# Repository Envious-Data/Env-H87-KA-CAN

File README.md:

# Env-H87-KA-CAN (May be renamed at some point)
Originally meant to be a keyboard for a comission I decided to re-work to a F12 TKL

## Main features
- Native ISO
- Hotswap
- Stepped Capslock (Optional)
- More to come

## Future plans
- Split Space space support
- Some indicator leds
- some kind of cyberpunk-y Lighting
- idk hidden cat symbol somewhere
- Weight but not really a weight

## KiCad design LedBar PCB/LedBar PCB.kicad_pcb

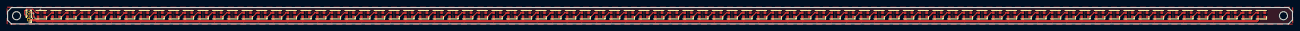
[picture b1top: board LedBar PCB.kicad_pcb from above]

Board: 2 copper layers, 349.7 x 4.4 mm, 88 parts (0 on the bottom side), 86 nets.

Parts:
C1: 100nF 0402; C_0402_1005Metric
D1, D2, D3, D4, D5, D6, D7, D8, D9, D10, D11, D12, D13, D14, D15, D16, D17, D18, D19, D20, D21, D22, D23, D24, D25, D26, D27, D28, D29, D30, D31, D32, D33, D34, D35, D36, D37, D38, D39, D40, D41, D42, D43, D44, D45, D46, D47, D48, D49, D50, D51, D52, D53, D54, D55, D56, D57, D58, D59, D60, D61, D62, D63, D64, D65, D66, D67, D68, D69, D70, D71, D72, D73, D74, D75, D76, D77, D78, D79, D80, D81, D82, D83, D84: WS2812B-2020; LED_WS2812B-2020_PLCC4_2.0x2.0mm
H1, H2: MountingHole; MountingHole_2.2mm_M2
J1: Conn_01x03; PinHeader_1x03_P1.00mm_Vertical

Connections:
+5V: C1.1, D1.4 (VDD), D2.4 (VDD), D3.4 (VDD), D4.4 (VDD), D5.4 (VDD), D6.4 (VDD), D7.4 (VDD), D8.4 (VDD), D9.4 (VDD), D10.4 (VDD), D11.4 (VDD), D12.4 (VDD), D13.4 (VDD), D14.4 (VDD), D15.4 (VDD), D16.4 (VDD), D17.4 (VDD), D18.4 (VDD), D19.4 (VDD), D20.4 (VDD), D21.4 (VDD), D22.4 (VDD), D23.4 (VDD), D24.4 (VDD), D25.4 (VDD), D26.4 (VDD), D27.4 (VDD), D28.4 (VDD), D29.4 (VDD), D30.4 (VDD), D31.4 (VDD), D32.4 (VDD), D33.4 (VDD), D34.4 (VDD), D35.4 (VDD), D36.4 (VDD), D37.4 (VDD), D38.4 (VDD), D39.4 (VDD), D40.4 (VDD), D41.4 (VDD), D42.4 (VDD), D43.4 (VDD), D44.4 (VDD), D45.4 (VDD), D46.4 (VDD), D47.4 (VDD), D48.4 (VDD), D49.4 (VDD), D50.4 (VDD), D51.4 (VDD), D52.4 (VDD), D53.4 (VDD), D54.4 (VDD), D55.4 (VDD), D56.4 (VDD), D57.4 (VDD), D58.4 (VDD), D59.4 (VDD), D60.4 (VDD), D61.4 (VDD), D62.4 (VDD), D63.4 (VDD), D64.4 (VDD), D65.4 (VDD), D66.4 (VDD), D67.4 (VDD), D68.4 (VDD), D69.4 (VDD), D70.4 (VDD), D71.4 (VDD), D72.4 (VDD), D73.4 (VDD), D74.4 (VDD), D75.4 (VDD), D76.4 (VDD), D77.4 (VDD), D78.4 (VDD), D79.4 (VDD), D80.4 (VDD), D81.4 (VDD), D82.4 (VDD), D83.4 (VDD), D84.4 (VDD), J1.1
DataIn: D1.3 (DIN), J1.2
GND: C1.2, D1.2 (VSS), D2.2 (VSS), D3.2 (VSS), D4.2 (VSS), D5.2 (VSS), D6.2 (VSS), D7.2 (VSS), D8.2 (VSS), D9.2 (VSS), D10.2 (VSS), D11.2 (VSS), D12.2 (VSS), D13.2 (VSS), D14.2 (VSS), D15.2 (VSS), D16.2 (VSS), D17.2 (VSS), D18.2 (VSS), D19.2 (VSS), D20.2 (VSS), D21.2 (VSS), D22.2 (VSS), D23.2 (VSS), D24.2 (VSS), D25.2 (VSS), D26.2 (VSS), D27.2 (VSS), D28.2 (VSS), D29.2 (VSS), D30.2 (VSS), D31.2 (VSS), D32.2 (VSS), D33.2 (VSS), D34.2 (VSS), D35.2 (VSS), D36.2 (VSS), D37.2 (VSS), D38.2 (VSS), D39.2 (VSS), D40.2 (VSS), D41.2 (VSS), D42.2 (VSS), D43.2 (VSS), D44.2 (VSS), D45.2 (VSS), D46.2 (VSS), D47.2 (VSS), D48.2 (VSS), D49.2 (VSS), D50.2 (VSS), D51.2 (VSS), D52.2 (VSS), D53.2 (VSS), D54.2 (VSS), D55.2 (VSS), D56.2 (VSS), D57.2 (VSS), D58.2 (VSS), D59.2 (VSS), D60.2 (VSS), D61.2 (VSS), D62.2 (VSS), D63.2 (VSS), D64.2 (VSS), D65.2 (VSS), D66.2 (VSS), D67.2 (VSS), D68.2 (VSS), D69.2 (VSS), D70.2 (VSS), D71.2 (VSS), D72.2 (VSS), D73.2 (VSS), D74.2 (VSS), D75.2 (VSS), D76.2 (VSS), D77.2 (VSS), D78.2 (VSS), D79.2 (VSS), D80.2 (VSS), D81.2 (VSS), D82.2 (VSS), D83.2 (VSS), D84.2 (VSS), J1.3
unnamed: D1.1 (DOUT), D2.3 (DIN)
unnamed: D2.1 (DOUT), D3.3 (DIN)
unnamed: D3.1 (DOUT), D4.3 (DIN)
unnamed: D4.1 (DOUT), D5.3 (DIN)
unnamed: D5.1 (DOUT), D6.3 (DIN)
unnamed: D6.1 (DOUT), D7.3 (DIN)
unnamed: D7.1 (DOUT), D8.3 (DIN)
unnamed: D8.1 (DOUT), D9.3 (DIN)
unnamed: D10.1 (DOUT), D11.3 (DIN)
unnamed: D9.1 (DOUT), D10.3 (DIN)
unnamed: D11.1 (DOUT), D12.3 (DIN)
unnamed: D12.1 (DOUT), D13.3 (DIN)
unnamed: D13.1 (DOUT), D14.3 (DIN)
unnamed: D14.1 (DOUT), D15.3 (DIN)
unnamed: D15.1 (DOUT), D16.3 (DIN)
unnamed: D16.1 (DOUT), D17.3 (DIN)
unnamed: D17.1 (DOUT), D18.3 (DIN)
unnamed: D18.1 (DOUT), D19.3 (DIN)
unnamed: D19.1 (DOUT), D20.3 (DIN)
unnamed: D20.1 (DOUT), D21.3 (DIN)
unnamed: D21.1 (DOUT), D22.3 (DIN)
unnamed: D22.1 (DOUT), D23.3 (DIN)
unnamed: D23.1 (DOUT), D24.3 (DIN)
unnamed: D24.1 (DOUT), D25.3 (DIN)
unnamed: D25.1 (DOUT), D26.3 (DIN)
unnamed: D26.1 (DOUT), D27.3 (DIN)
unnamed: D27.1 (DOUT), D28.3 (DIN)
unnamed: D28.1 (DOUT), D29.3 (DIN)
unnamed: D29.1 (DOUT), D30.3 (DIN)
unnamed: D30.1 (DOUT), D31.3 (DIN)
unnamed: D31.1 (DOUT), D32.3 (DIN)
unnamed: D32.1 (DOUT), D33.3 (DIN)
unnamed: D33.1 (DOUT), D34.3 (DIN)
unnamed: D34.1 (DOUT), D35.3 (DIN)
unnamed: D35.1 (DOUT), D36.3 (DIN)
unnamed: D36.1 (DOUT), D37.3 (DIN)
unnamed: D37.1 (DOUT), D38.3 (DIN)
unnamed: D38.1 (DOUT), D39.3 (DIN)
unnamed: D39.1 (DOUT), D40.3 (DIN)
unnamed: D40.1 (DOUT), D41.3 (DIN)
unnamed: D41.1 (DOUT), D42.3 (DIN)
unnamed: D42.1 (DOUT), D43.3 (DIN)
unnamed: D43.1 (DOUT), D44.3 (DIN)
unnamed: D44.1 (DOUT), D45.3 (DIN)
unnamed: D45.1 (DOUT), D46.3 (DIN)
unnamed: D46.1 (DOUT), D47.3 (DIN)
unnamed: D47.1 (DOUT), D48.3 (DIN)
unnamed: D48.1 (DOUT), D49.3 (DIN)
unnamed: D49.1 (DOUT), D50.3 (DIN)
unnamed: D50.1 (DOUT), D51.3 (DIN)
unnamed: D51.1 (DOUT), D52.3 (DIN)
unnamed: D52.1 (DOUT), D53.3 (DIN)
unnamed: D53.1 (DOUT), D54.3 (DIN)
unnamed: D54.1 (DOUT), D55.3 (DIN)
unnamed: D55.1 (DOUT), D56.3 (DIN)
unnamed: D56.1 (DOUT), D57.3 (DIN)
unnamed: D57.1 (DOUT), D58.3 (DIN)
unnamed: D58.1 (DOUT), D59.3 (DIN)
unnamed: D59.1 (DOUT), D60.3 (DIN)
unnamed: D60.1 (DOUT), D61.3 (DIN)
unnamed: D61.1 (DOUT), D62.3 (DIN)
unnamed: D62.1 (DOUT), D63.3 (DIN)
unnamed: D63.1 (DOUT), D64.3 (DIN)
unnamed: D64.1 (DOUT), D65.3 (DIN)
unnamed: D65.1 (DOUT), D66.3 (DIN)
unnamed: D66.1 (DOUT), D67.3 (DIN)
unnamed: D67.1 (DOUT), D68.3 (DIN)
unnamed: D68.1 (DOUT), D69.3 (DIN)
unnamed: D69.1 (DOUT), D70.3 (DIN)
unnamed: D70.1 (DOUT), D71.3 (DIN)
unnamed: D71.1 (DOUT), D72.3 (DIN)
unnamed: D72.1 (DOUT), D73.3 (DIN)
unnamed: D73.1 (DOUT), D74.3 (DIN)
unnamed: D74.1 (DOUT), D75.3 (DIN)
unnamed: D75.1 (DOUT), D76.3 (DIN)
unnamed: D76.1 (DOUT), D77.3 (DIN)
unnamed: D77.1 (DOUT), D78.3 (DIN)
unnamed: D78.1 (DOUT), D79.3 (DIN)
unnamed: D79.1 (DOUT), D80.3 (DIN)
unnamed: D80.1 (DOUT), D81.3 (DIN)
unnamed: D81.1 (DOUT), D82.3 (DIN)
unnamed: D82.1 (DOUT), D83.3 (DIN)
unnamed: D83.1 (DOUT), D84.3 (DIN)

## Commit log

2022-12-04 Committed all current changes
2022-12-04 properly renamed files
2022-12-04 general progress
2022-12-04 small cleanup
2022-12-05 slight rework to F12 TKL
2022-12-05 various fixes and adjustments
2022-12-05 rename some files
2022-12-05 a lot of general re-work
2022-12-05 lots of progress toward wiring up MCU and also added missing crystal
2022-12-06 undo of some work and rotated a switch due to physical incompatibility with case
2022-12-06 some temporary DXFs while I re-do the case again
2022-12-08 renamed main folder and also created led bar pcb, need to implement some connector on the main PCB for this
2022-12-20 wired up a whole bunch of matrix traces, now just need to add some I2C headers and some RGB connectors and some hidden cats among other illicit things like memes.
2023-01-26 added a GPIO breakout
